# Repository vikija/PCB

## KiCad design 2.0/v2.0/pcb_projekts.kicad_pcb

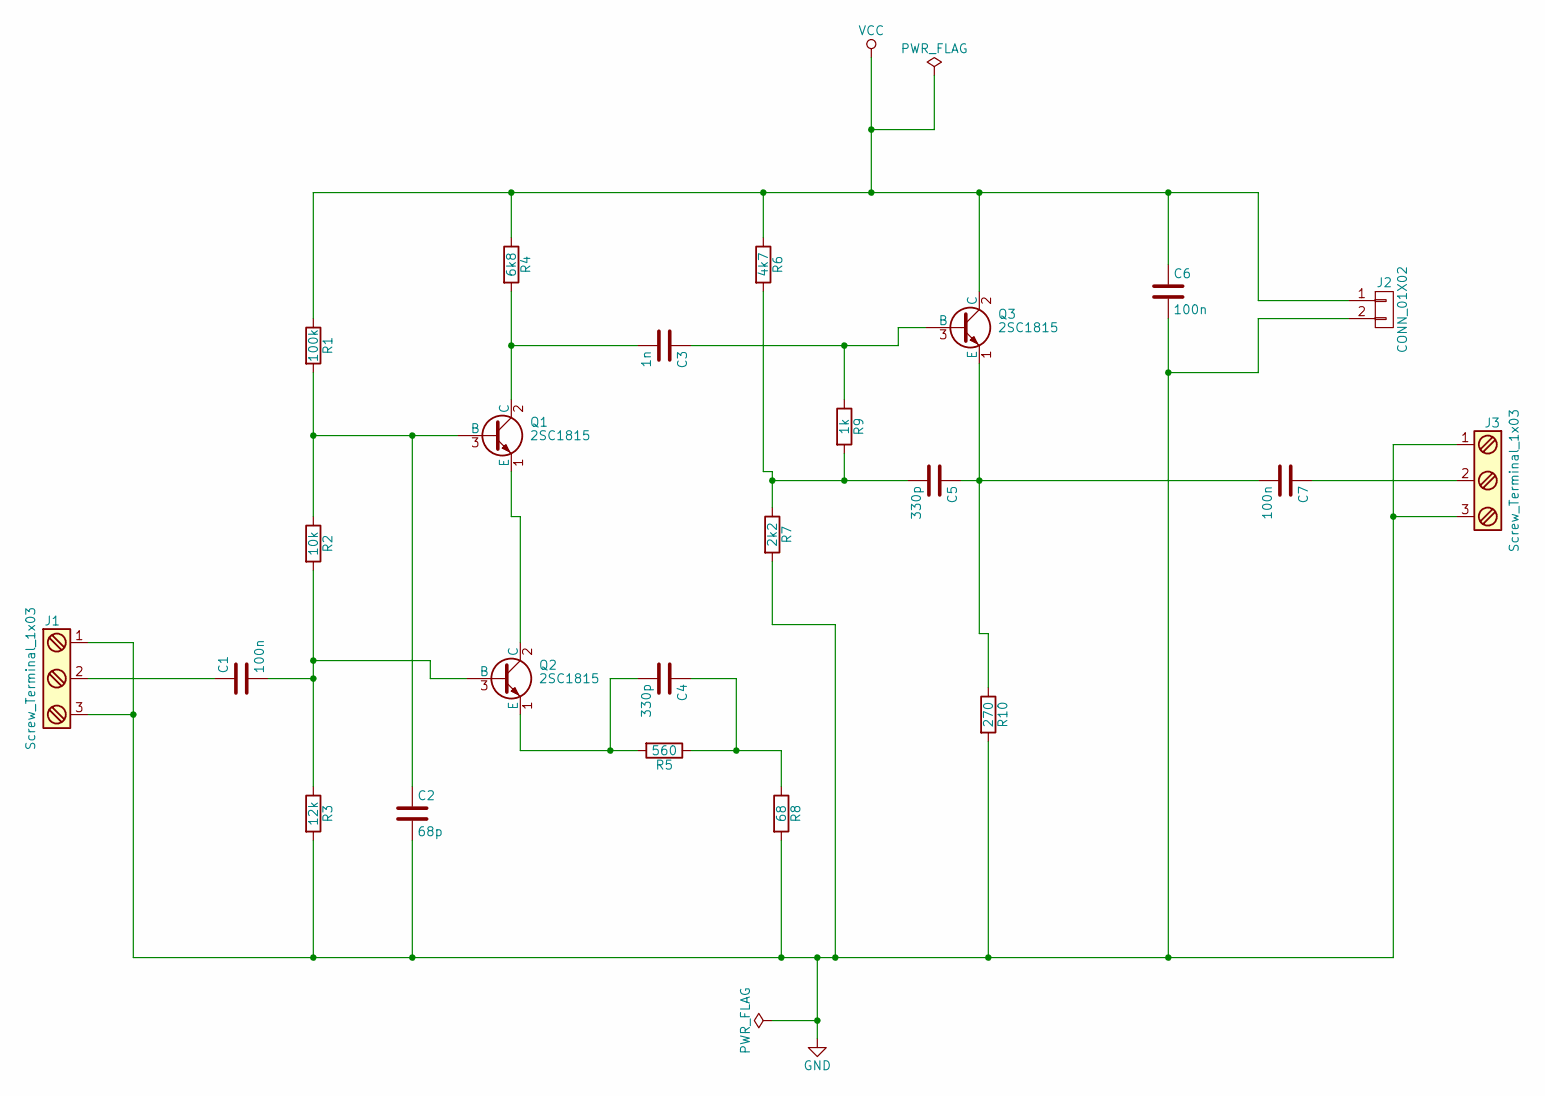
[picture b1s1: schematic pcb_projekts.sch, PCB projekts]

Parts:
C1, C6, C7: 100n; C_Disc_D5.0mm_W2.5mm_P5.00mm
C2: 68p; C_Disc_D5.0mm_W2.5mm_P5.00mm
C3: 1n; C_Disc_D5.0mm_W2.5mm_P5.00mm
C4, C5: 330p; C_Disc_D5.0mm_W2.5mm_P5.00mm
J1, J3: Screw_Terminal_1x03; bornier3
J2: CONN_01X02; Pin_Header_Straight_1x02_Pitch1.27mm
Q1, Q2, Q3: 2SC1815; TO-92_Molded_Narrow
R1: 100k; R_Axial_DIN0204_L3.6mm_D1.6mm_P5.08mm_Horizontal
R2: 10k; R_Axial_DIN0204_L3.6mm_D1.6mm_P5.08mm_Horizontal
R3: 12k; R_Axial_DIN0204_L3.6mm_D1.6mm_P5.08mm_Horizontal
R4: 6k8; R_Axial_DIN0204_L3.6mm_D1.6mm_P5.08mm_Horizontal
R5: 560; R_Axial_DIN0204_L3.6mm_D1.6mm_P5.08mm_Horizontal
R6: 4k7; R_Axial_DIN0204_L3.6mm_D1.6mm_P5.08mm_Horizontal
R7: 2k2; R_Axial_DIN0204_L3.6mm_D1.6mm_P5.08mm_Horizontal
R8: 68; R_Axial_DIN0204_L3.6mm_D1.6mm_P5.08mm_Horizontal
R9: 1k; R_Axial_DIN0204_L3.6mm_D1.6mm_P5.08mm_Horizontal
R10: 270; R_Axial_DIN0204_L3.6mm_D1.6mm_P5.08mm_Horizontal

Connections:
GND: C2.2, C6.2, J1.1, J1.3, J2.2, J3.1, J3.3, R3.2, R7.2, R8.2, R10.2
unnamed: C1.1, J1.2
unnamed: C1.2, Q2.3 (B), R2.2, R3.1
unnamed: C2.1, Q1.3 (B), R1.2, R2.1
unnamed: C3.1, Q3.3 (B), R9.1
unnamed: C3.2, Q1.2 (C), R4.2
unnamed: C4.1, R5.1, R8.1
unnamed: C4.2, Q2.1 (E), R5.2
unnamed: C5.1, C7.2, Q3.1 (E), R10.1
unnamed: C5.2, R6.2, R7.1, R9.2
unnamed: C7.1, J3.2
unnamed: Q1.1 (E), Q2.2 (C)
VCC: C6.1, J2.1, Q3.2 (C), R1.1, R4.1, R6.1

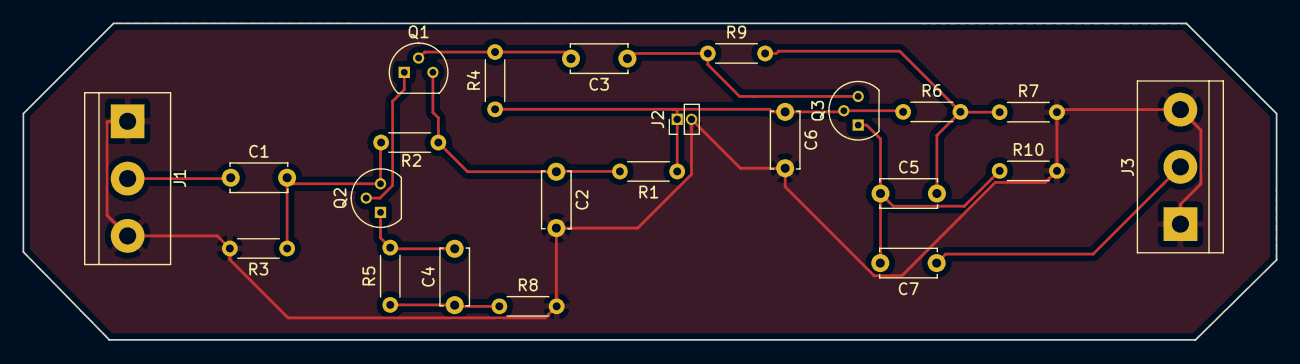
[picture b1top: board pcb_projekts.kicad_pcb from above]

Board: 2 copper layers, 111.2 x 28.1 mm, 23 parts (0 on the bottom side), 13 nets.

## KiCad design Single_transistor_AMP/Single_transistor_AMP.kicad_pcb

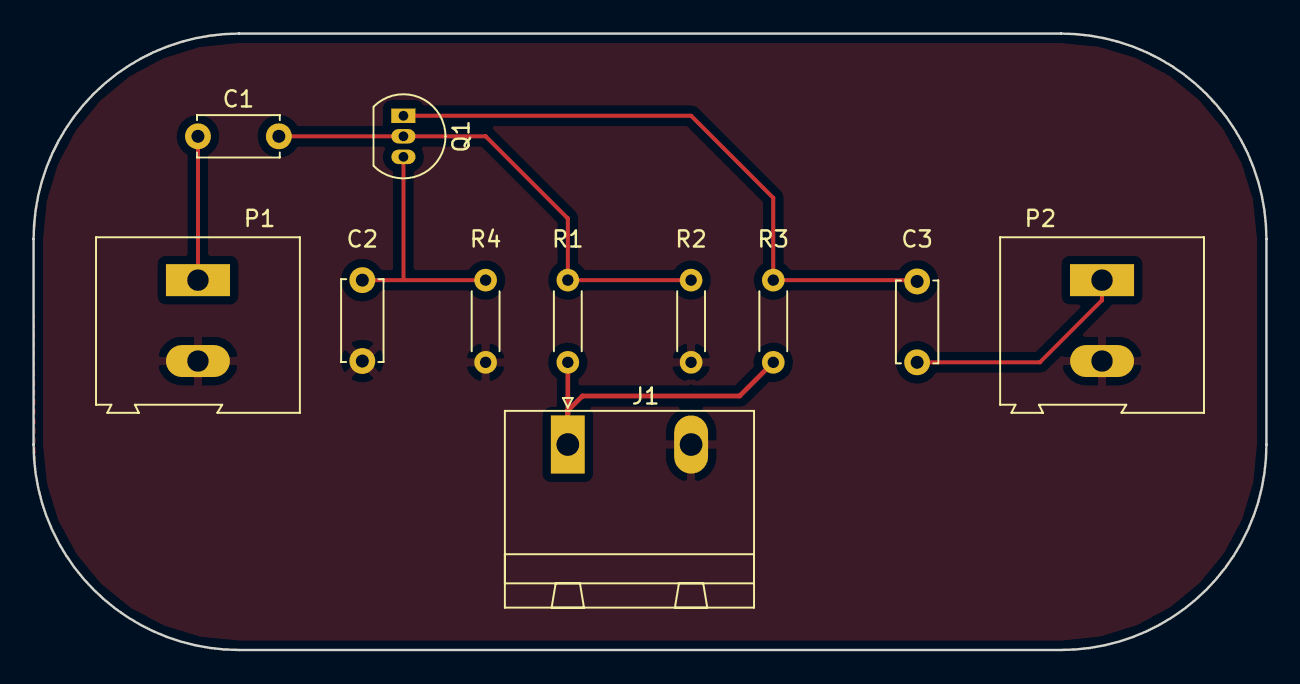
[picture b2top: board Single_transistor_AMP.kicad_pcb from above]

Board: 2 copper layers, 76.2 x 38.1 mm, 11 parts (0 on the bottom side), 7 nets.

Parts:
C1, C3: 20uF; C_Disc_D5.0mm_W2.5mm_P5.00mm
C2: 50uF; C_Disc_D5.0mm_W2.5mm_P5.00mm
J1: Power_Con; PhoenixContact_GMSTBA-G_02x7.62mm_Angled
P1: Signal_In; AK300-2
P2: Signal_Out; AK300-2
Q1: BC548; TO-92_Inline_Narrow_Oval
R1: 22k; R_Axial_DIN0204_L3.6mm_D1.6mm_P5.08mm_Horizontal
R2: 6.8k; R_Axial_DIN0204_L3.6mm_D1.6mm_P5.08mm_Horizontal
R3: 4.7k; R_Axial_DIN0204_L3.6mm_D1.6mm_P5.08mm_Horizontal
R4: 1.8k; R_Axial_DIN0204_L3.6mm_D1.6mm_P5.08mm_Horizontal

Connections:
+12V: J1.1, R1.1, R3.1
GND: C2.2, J1.2, P1.2, P2.2, R2.2, R4.2
unnamed: C1.1, P1.1
unnamed: C1.2, Q1.2, R1.2, R2.1
unnamed: C2.1, Q1.3, R4.1
unnamed: C3.1, Q1.1, R3.2
unnamed: C3.2, P2.1

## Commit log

2017-03-02 README update to test Github Repo
2017-05-10 majas darbs
2017-06-12 majas darbi
2017-06-12 Battery
2017-06-17 Kursa darbs
